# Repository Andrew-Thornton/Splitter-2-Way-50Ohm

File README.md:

# Splitter-2-Way-50Ohm

This GitHub repository provides a design for a **50-ohm RF splitter**.  
It currently uses **KiCad 10.0** and is being tested on **Ubuntu 24.04**.

---

## Installation Instructions

### 1. General Git Repository Setup

Initialize the repository and its submodules:

```bash
git submodule update --init --recursive
```

### 2. Kicad
Add the KiCad PPA, update your package list, and install KiCad:
```bash
sudo add-apt-repository ppa:kicad/kicad-10.0-releases  
sudo apt update  
sudo apt install kicad  
```

### 3. OpenEMS
Install Required Packages:
```bash
sudo apt-get update  
sudo apt-get install build-essential \  
                       cmake \  
                       git \  
                       libhdf5-dev \  
                       libboost-all-dev \  
                       libcgal-dev \  
                       libtinyxml-dev \  
                       qtbase5-dev \  
                       libvtk9-dev \  
                       libvtk9-qt-dev \  
                       gengetopt \  
                       help2man \  
                       groff \  
                       pod2pdf \  
                       bison \  
                       flex \  
                       libhpdf-dev \  
                       libtool  \
```

**Set Up Python Virtual Environment for OpenEMS**
Run the setup script and activate the virtual environment:
```bash
./setup_venv.sh
```
 
Note the second time you can just run
```bash
source .venv/bin/activate
```

**Running the simulation**
```bash
cd sim
python ./pcb_large_sim.py --plot
```

Note this is still a work in progress

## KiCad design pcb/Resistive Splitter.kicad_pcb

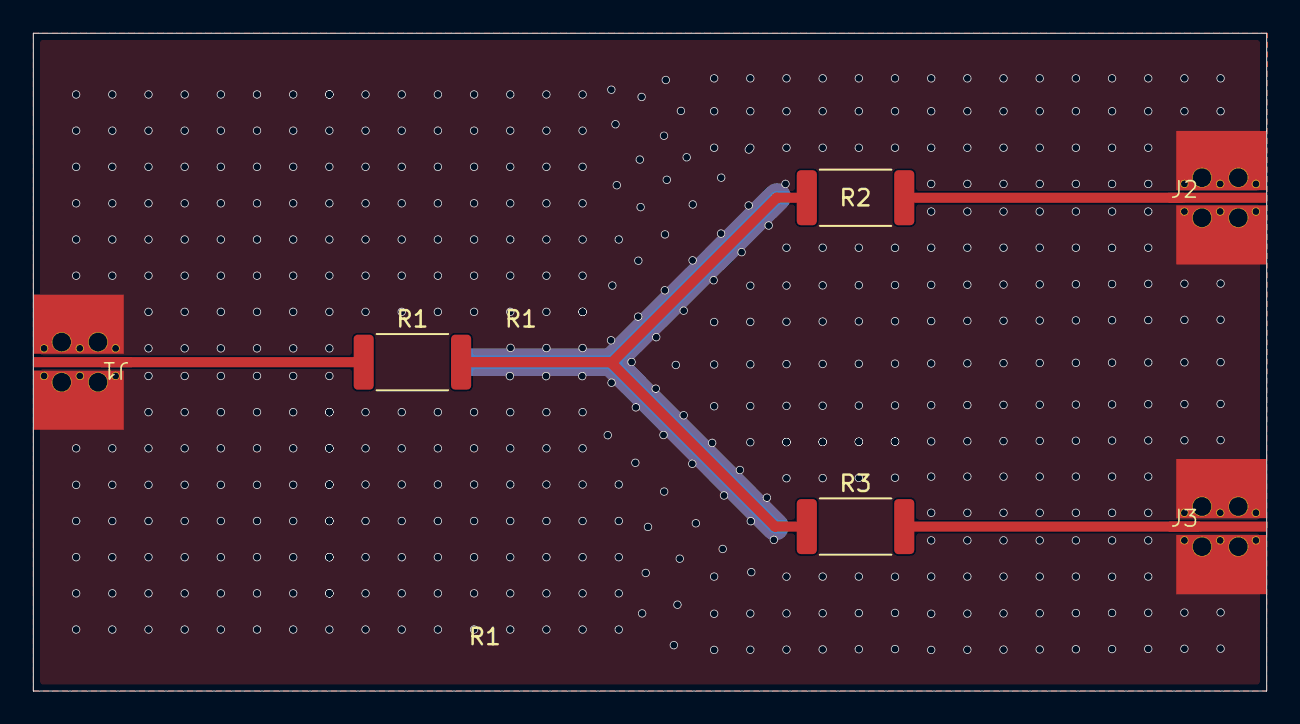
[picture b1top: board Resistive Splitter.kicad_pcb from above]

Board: 2 copper layers, 75.0 x 40.0 mm, 6 parts (0 on the bottom side), 3 nets.

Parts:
J1, J2, J3: SMA 50; Amphenol 901-10510-2
R1, R2, R3: 16R; R_2512_6332Metric

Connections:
GND: J1.2 (Ext), J2.2 (Ext), J3.2 (Ext)
unnamed: J2.1 (In), R2.2
unnamed: R1.2, R2.1, R3.1

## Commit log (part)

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2025-11-12 initial commit with pcb, schematic, and project file
2025-11-12 readme
